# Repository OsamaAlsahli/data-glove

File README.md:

# Data Glove

Low-cost, high-accuracy data glove with real-time hand motion tracking and
fingertip force sensing.

Final Year Project — **Osama Alsahli**, BEng Electronic Engineering, University
of York, 2026.

## What this is

A wearable glove that captures finger and hand orientation using sixteen
BNO055 9-axis IMUs (one per finger phalanx plus one on the dorsum), with
soft optical tactile sensors (STOF) at the fingertips for contact force.
Quaternion data is streamed from an ESP32 over USB serial to a Python
bridge, which serves it to the FSGlove visualisation framework via gRPC.

Headline hardware bill of materials: 16× BNO055 IMUs, 2× TCA9548A I2C
multiplexers, one ESP32 dev board, soft Ecoflex 00-30 STOF sensors at the
fingertips. Total cost of purchased electronics ≈ £105.

For the full report (motivation, lit review, design, evaluation), see the
accompanying BEng final report.

## Repository layout

```
firmware/         ESP32 Arduino sketches (C++)
  adafruit_test/  Single-BNO055 smoke test
  tst/            Single sensor through TCA9548A
  tst2/           TCA9548A I2C scanner
  webserial_3d/   Single sensor for the Adafruit WebSerial 3D viewer
  quat_finger/    4-IMU single-finger demo
  quat/           Full 16-IMU glove firmware
  fsglove-main/   FSGlove visualisation framework (third-party, included
                  for reproducibility - see Licence section)

bridge/           Python serial-to-gRPC bridge
  bridge.py            Full 16-sensor bridge (the one you actually run)
  bridge_finger.py     Incomplete 4-sensor variant, kept for reference
  read_imu.py          Minimal serial quaternion printer
  visualise_imu.py     Live OpenGL "bone" visualiser

images/           Prototype photos, kinematic model, Gantt chart
schematics/       PCB / schematic designs (KiCad) for STOF and main board
```

## How to flash the firmware

1. Open `firmware/quat/quat.ino` in the Arduino IDE.
2. Install the **Adafruit BNO055** and **Adafruit Unified Sensor** libraries
   from the Library Manager.
3. Select the ESP32 board, the matching USB serial port, and upload.

The single-sensor bring-up sketches (`adafruit_test`, `tst`, `tst2`,
`webserial_3d`) are useful for verifying hardware before flashing the full
build.

## How to run the bridge

```bash
cd bridge
pip install pyserial grpcio
# Generate imu_packet_pb2.py / imu_packet_pb2_grpc.py from the FSGlove proto
# (imu_packet.proto lives inside firmware/fsglove-main).
python bridge.py
```

The bridge listens on `localhost:18890`; start FSGlove afterwards and it
will subscribe to the stream.

If you want to drive the visualiser without hardware, swap the
`target=read_serial` line in `bridge.py`'s `main()` for
`target=generate_fake_serial`.

## Licence

The code I wrote (everything under `firmware/` except `fsglove-main/`, and
everything under `bridge/`) is released for academic and personal use.

`firmware/fsglove-main/` is included for reproducibility only and is the
work of its original authors — see its own README and licence inside that
folder or (<https://github.com/davidliyutong/fsglove>). The SMPLH model weights (`SMPLH_male.pkl`, `SMPLH_female.pkl`)
required by FSGlove are **not** included in this repo. To obtain them and
get FSGlove running, follow the setup instructions in the upstream FSGlove
repository (<https://github.com/davidliyutong/fsglove>); the project page
is at <https://sites.google.com/view/fsglove/>.

## Known limitations

- **Single multiplexer firmware.** `firmware/quat/quat.ino` was written
  assuming one 16 channel multiplexer, but the final hardware splits the
  16 IMUs across two TCA9548As (each with 8 channels). Reading sensors 8 to 15
  therefore needs a second multiplexer select layer that this build does
  not yet implement. The limitation is flagged inline with a `NOTE:` comment.
  The single finger and 8 sensor paths are fully working.
- `bridge/bridge_finger.py` is an unfinished early version of the bridge,
  kept for historical reference. The working bridge is `bridge/bridge.py`.

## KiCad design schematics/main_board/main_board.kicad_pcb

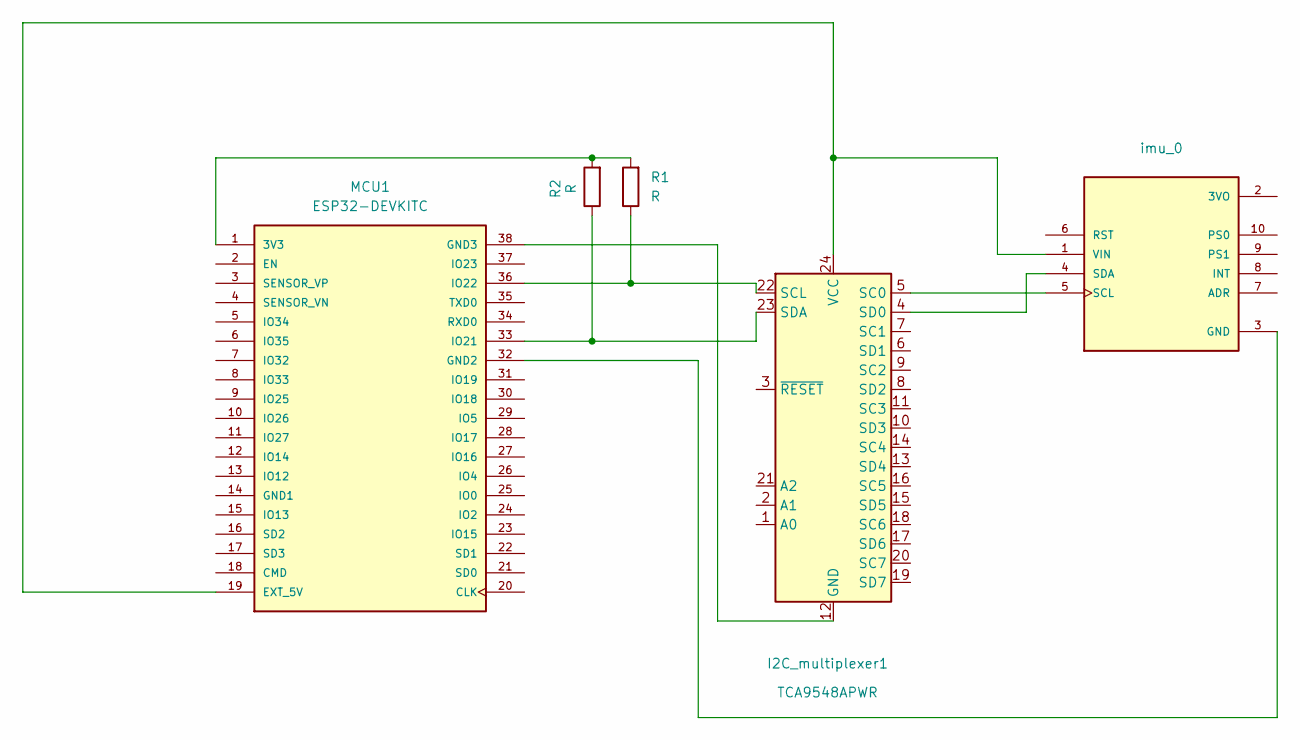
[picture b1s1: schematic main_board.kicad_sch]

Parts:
I2C_multiplexer1: TCA9548APWR; TSSOP-24_4.4x7.8mm_P0.65mm
MCU1: ESP32-DEVKITC; PARTREV N/A
R1, R2: R; R_0603_1608Metric
imu_0: MODULE_2472; PARTREV N/A

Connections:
unnamed: I2C_multiplexer1.12 (GND), MCU1.38 (GND3)
unnamed: I2C_multiplexer1.5 (SC0), imu_0.5 (SCL)
unnamed: I2C_multiplexer1.22 (SCL), MCU1.36 (IO22), R1.1
unnamed: I2C_multiplexer1.4 (SD0), imu_0.4 (SDA)
unnamed: I2C_multiplexer1.23 (SDA), MCU1.33 (IO21), R2.1
unnamed: I2C_multiplexer1.24 (VCC), MCU1.19 (EXT_5V), imu_0.1 (VIN)
unnamed: MCU1.1 (3V3), R1.2, R2.2
unnamed: MCU1.32 (GND2), imu_0.3 (GND)

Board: 2 copper layers, 5 parts (0 on the bottom side), 8 nets, no tracks yet.

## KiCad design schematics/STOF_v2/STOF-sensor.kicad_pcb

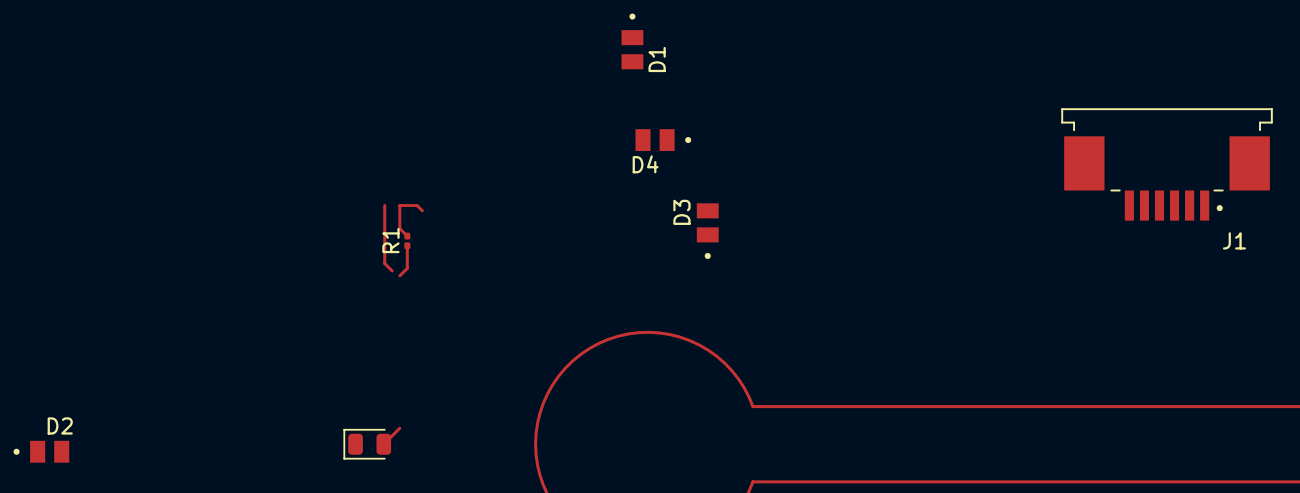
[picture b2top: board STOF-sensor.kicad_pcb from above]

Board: 2 copper layers, 7 parts (0 on the bottom side), 8 nets.

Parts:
D1, D2, D3, D4: TEMD7000X01; XDCR_TEMD7000X01
J1: 84953-6; TE_84953-6
LED1: LED; LED_0805_2012Metric
R1: 100; R_0201_0603Metric

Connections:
+5V: D1.C, D2.C, D3.C, D4.C, J1.1, R1.2
GND: J1.2, LED1.1 (K)
unnamed: D1.A, J1.3
unnamed: D2.A, J1.4
unnamed: D3.A, J1.5
unnamed: D4.A, J1.6
unnamed: J1.S1 (SHIELD), J1.S2 (SHIELD)
unnamed: LED1.2 (A), R1.1

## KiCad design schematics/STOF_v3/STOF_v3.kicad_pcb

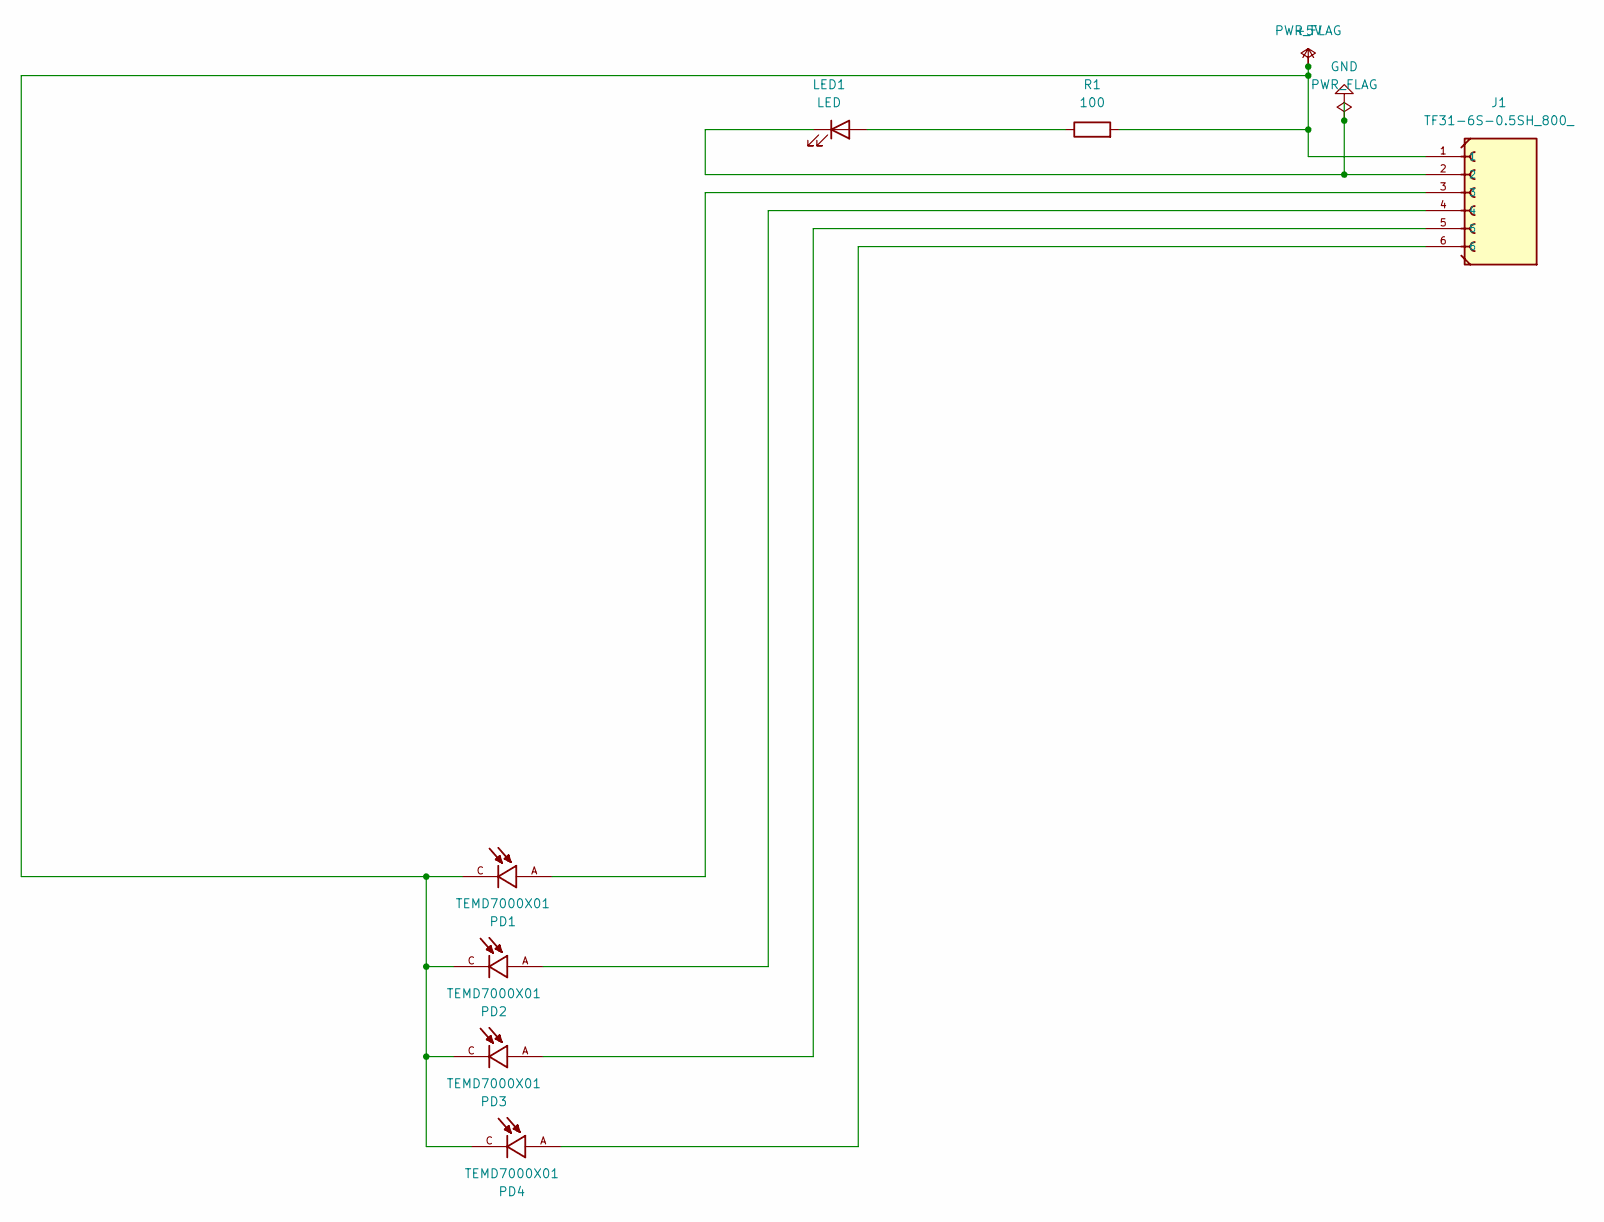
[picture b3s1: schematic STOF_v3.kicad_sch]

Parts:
J1: TF31-6S-0.5SH_800_; HRS_TF31-6S-0.5SH_800_
LED1: LED; LED_0805_2012Metric
PD1, PD2, PD3, PD4: TEMD7000X01; XDCR_TEMD7000X01
R1: 100; R_0201_0603Metric

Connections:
+5V: J1.1, PD1.C, PD2.C, PD3.C, PD4.C, R1.2
GND: J1.2, LED1.1 (K)
unnamed: J1.3, PD1.A
unnamed: J1.4, PD2.A
unnamed: J1.5, PD3.A
unnamed: J1.6, PD4.A
unnamed: LED1.2 (A), R1.1

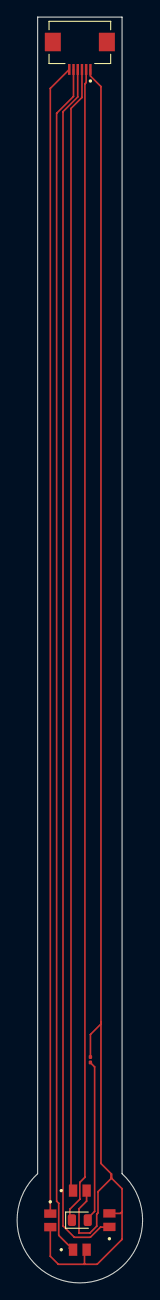
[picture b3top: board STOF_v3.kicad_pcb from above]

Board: 2 copper layers, 14.9 x 149.9 mm, 7 parts (0 on the bottom side), 7 nets.

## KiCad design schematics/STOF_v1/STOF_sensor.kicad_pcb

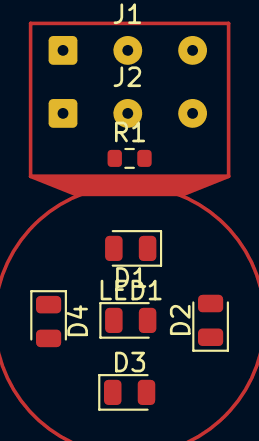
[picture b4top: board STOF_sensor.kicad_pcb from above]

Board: 2 copper layers, 8 parts (0 on the bottom side), 7 nets, no tracks yet.

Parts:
D1, D2, D3, D4: TEMD7000X01; LED_0805_2012Metric
J1, J2: Conn_01x03; SolderWire-0.1sqmm_1x03_P3.6mm_D0.4mm_OD1mm
LED1: LED; LED_0805_2012Metric
R1: 100; R_0603_1608Metric

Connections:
+5V: D1.1 (K), D2.1 (K), D3.1 (K), D4.1 (K), J1.1, R1.1
GND: J1.2, LED1.1 (K)
unnamed: D1.2 (A), J1.3
unnamed: D2.2 (A), J2.1
unnamed: D3.2 (A), J2.2
unnamed: D4.2 (A), J2.3
unnamed: LED1.2 (A), R1.2
